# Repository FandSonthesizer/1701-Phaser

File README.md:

# 1701-Phaser 
This is a very nice phaser using a LM13700 OTA for the phasing effect, a LFO and some buffers to create the effect.
All run-of the-mill parts, fits into a 1590b enclosure and just sounds lovely.  
Check the demo on our youtube video blog for sound examples: https://www.youtube.com/channel/UCoEb9FIM5uLZekRLUyaKJfA

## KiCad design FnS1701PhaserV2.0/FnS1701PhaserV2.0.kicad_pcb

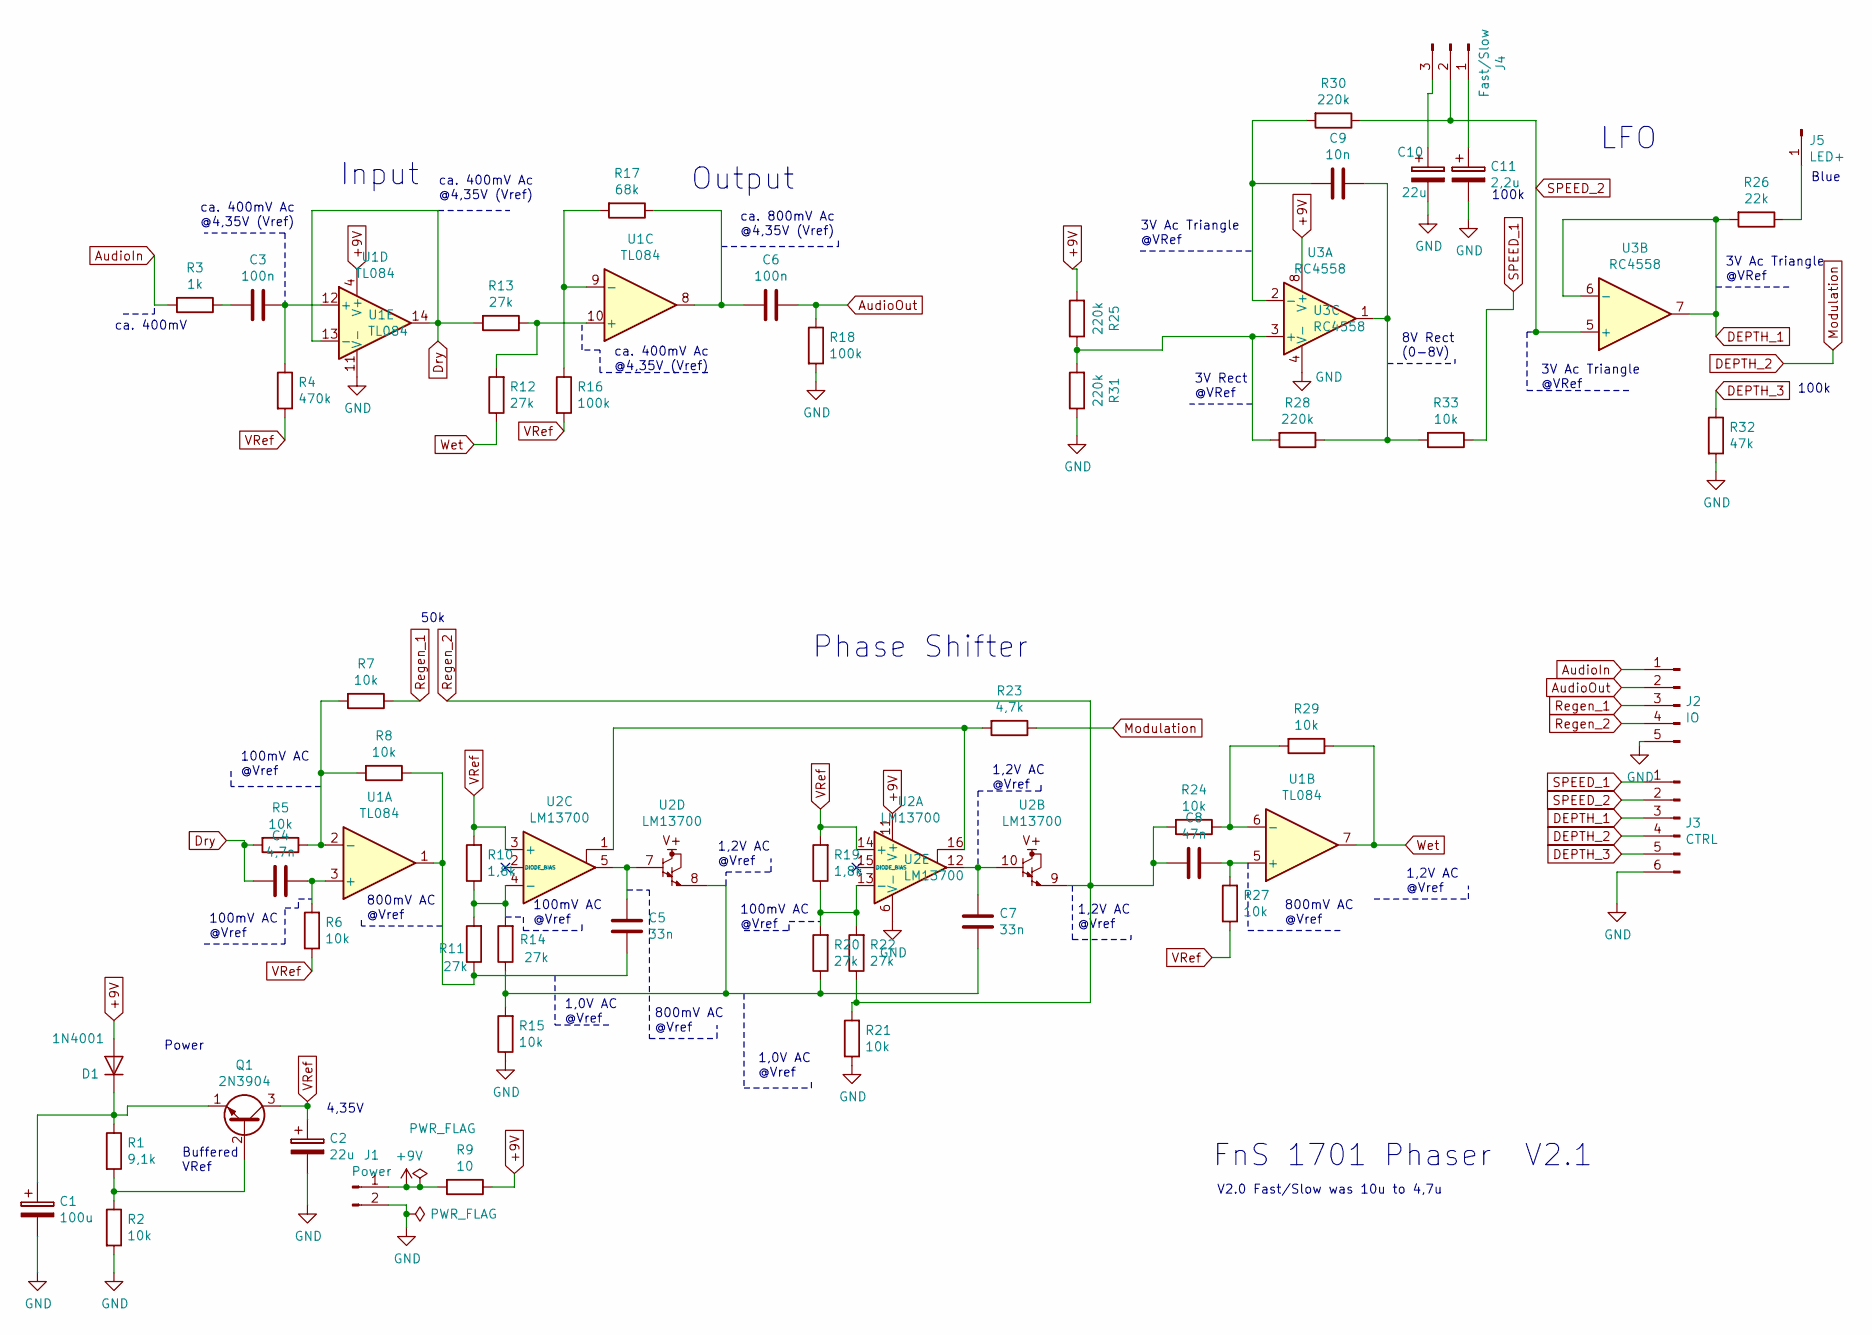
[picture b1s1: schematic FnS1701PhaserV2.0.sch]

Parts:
C1: 100u; Elko_D6.3mm_P2.50mm
C2, C10: 22u; Elko_D6.3mm_P2.50mm
C3, C6: 100n; Kondensator_Keramik
C4: 4,7n; Kondensator_Keramik
C5, C7: 33n; Kondensator_Keramik
C8: 47n; Kondensator_Keramik
C9: 10n; Kondensator_Keramik
C11: 2,2u; Elko_D6.3mm_P2.50mm
D1: 1N4001; Diode_Horizontal
J1: Power; Stift_x02
J2: IO; PinHeader_1x05_P2.54mm_Vertical
J3: CTRL; PinHeader_1x06_P2.54mm_Vertical_NIK
J4: Fast/Slow; Stift_0x3
J5: LED+; Stift
Q1: 2N3904; TO-92_Wide_NIK
R1: 9,1k; Widerstand_liegend
R2, R5, R6, R7, R8, R15, R21, R24, R27, R29, R33: 10k; Widerstand_liegend
R3: 1k; Widerstand_liegend
R4: 470k; Widerstand_liegend
R9: 10; Widerstand_liegend
R10, R19: 1,8k; Widerstand_liegend
R11, R12, R13, R14, R20, R22: 27k; Widerstand_liegend
R16, R18: 100k; Widerstand_liegend
R17: 68k; Widerstand_liegend
R23: 4,7k; Widerstand_liegend
R25, R28, R30, R31: 220k; Widerstand_liegend
R26: 22k; Widerstand_liegend
R32: 47k; Widerstand_liegend
U1: TL084; DIP-14_W7.62mm_Socket_LongPads
U2: LM13700; DIP-16_W7.62mm_Socket_LongPads
U3: RC4558; DIP-8_W7.62mm_Socket_LongPads

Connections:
+9V: D1.2 (A), J1.1, R9.1, R9.2, R25.2, U1.4 (V+), U2.11 (V+), U3.8 (V+)
AudioIn: J2.1, R3.2
AudioOut: C6.1, J2.2, R18.1
DEPTH_1: J3.3, R26.2, U3.6 (-), U3.7
DEPTH_2: J3.4, R23.1
DEPTH_3: J3.5, R32.1
Dry: C4.2, R5.2, R13.2, U1.13 (-), U1.14
GND: C1.2, C2.2, C10.2, C11.2, J1.2, J2.5, J3.6, R2.2, R15.1, R18.2, R21.1, R31.1, R32.2, U1.11 (V-), U2.6 (V-), U3.4 (V-)
unnamed: C1.1, D1.1 (K), Q1.1 (E), R1.1
unnamed: C3.1, R4.1, U1.12 (+)
unnamed: C3.2, R3.1
unnamed: C4.1, R6.2, U1.3 (+)
unnamed: C5.1, R8.1, R11.1, U1.1
unnamed: C5.2, U2.5, U2.7
unnamed: C6.2, R17.1, U1.8
unnamed: C7.1, R14.1, R15.2, R20.1, U2.8
unnamed: C7.2, U2.10, U2.12
unnamed: C8.1, R27.2, U1.5 (+)
unnamed: C9.1, R28.1, R33.2, U3.1
unnamed: C9.2, R30.2, U3.2 (-)
unnamed: C10.1, J4.3
unnamed: C11.1, J4.1
unnamed: J5.1, R26.1
unnamed: Q1.2 (B), R1.2, R2.1
unnamed: R5.1, R7.2, R8.2, U1.2 (-)
unnamed: R10.1, R11.2, R14.2, U2.4 (-)
unnamed: R12.2, R13.1, U1.10 (+)
unnamed: R16.1, R17.2, U1.9 (-)
unnamed: R19.1, R20.2, R22.2, U2.13 (-)
unnamed: R23.2, U2.1, U2.16
unnamed: R24.1, R29.2, U1.6 (-)
unnamed: R25.1, R28.2, R31.2, U3.3 (+)
Regen_1: J2.3, R7.1
Regen_2: C8.2, J2.4, R21.2, R22.1, R24.2, U2.9
SPEED_1: J3.1, R33.1
SPEED_2: J3.2, J4.2, R30.1, U3.5 (+)
VRef: C2.1, Q1.3 (C), R4.2, R6.1, R10.2, R16.2, R19.2, R27.1, U2.3 (+), U2.14 (+)
Wet: R12.1, R29.1, U1.7

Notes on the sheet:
Input
Output
Power
LFO
Phase Shifter
FnS 1701 Phaser V2.1
100k
50k
4,35V
ca. 400mV
ca. 400mV Ac @4,35V (Vref)
ca. 800mV Ac @4,35V (Vref)
3V Ac Triangle @VRef
8V Rect (0-8V)
3V Rect @VRef
Buffered VRef
100mV AC @Vref
800mV AC @Vref
1,2V AC @Vref
1,0V AC @Vref
Blue
V2.0 Fast/Slow was 10u to 4,7u

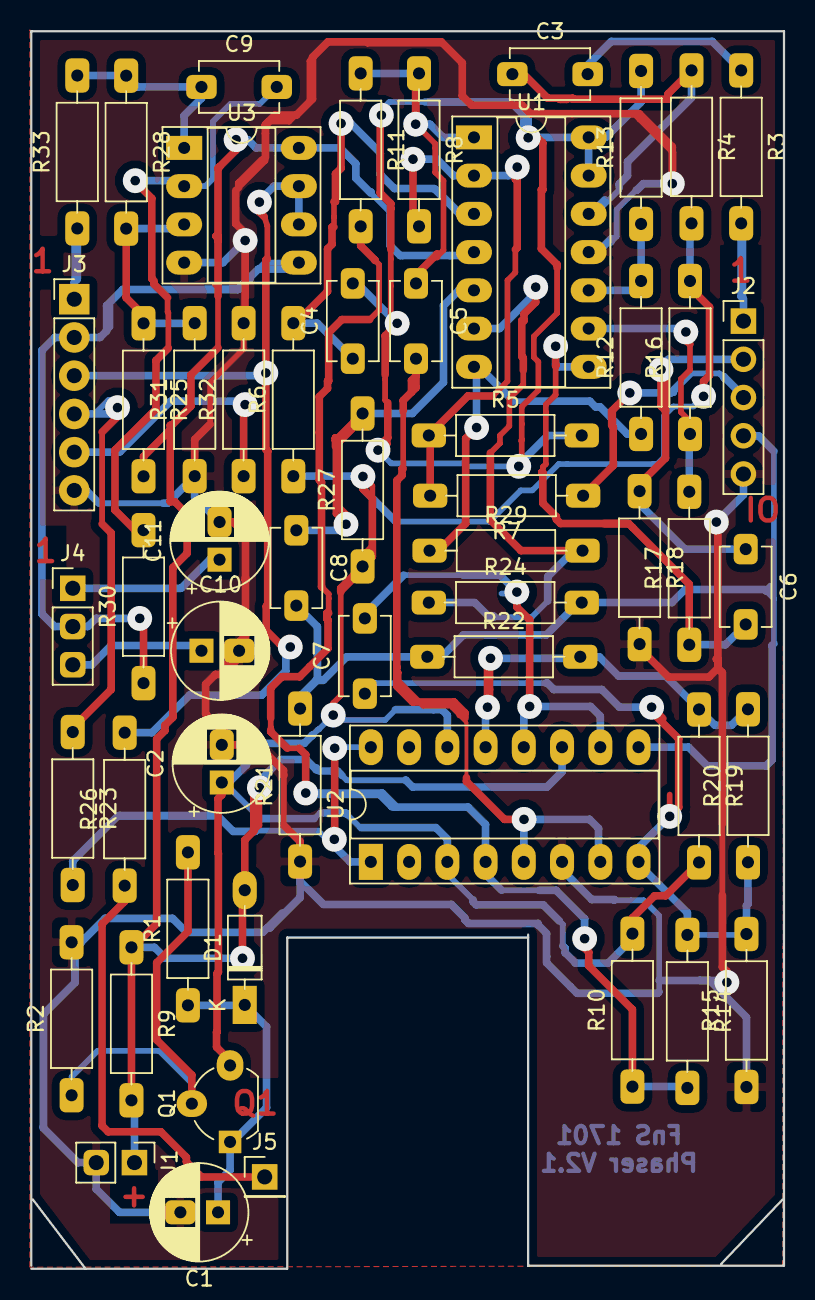
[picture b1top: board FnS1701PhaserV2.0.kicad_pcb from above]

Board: 2 copper layers, 50.0 x 82.2 mm, 54 parts (0 on the bottom side), 38 nets.
